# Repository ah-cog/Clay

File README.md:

Clay
====

Clay is an intelligent material that anyone can use to create interactive systems in objects and environments.

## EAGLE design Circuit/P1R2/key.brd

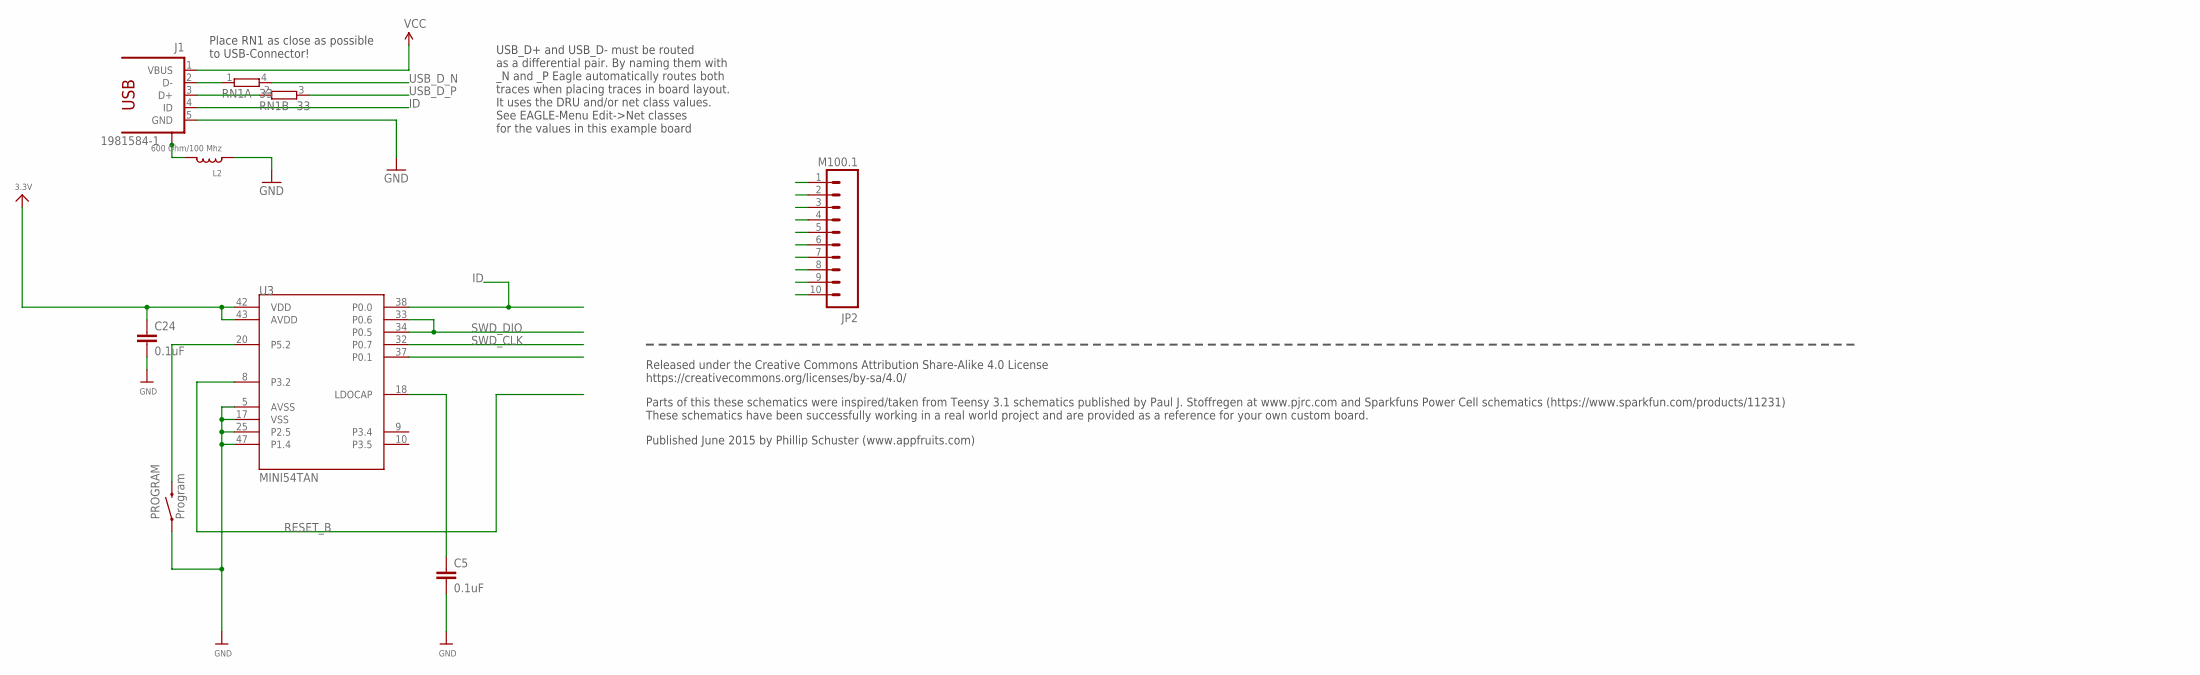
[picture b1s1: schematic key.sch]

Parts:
C5, C24: 0.1uF; 0603-CAP
J1: 1981584-1; MPN ZX62-AB-5PA(11)
JP2: M100.1; 1X10
L2: 600 Ohm/100 Mhz; 0805
PROGRAM: Program; TACTILE-SWITCH-1101NE; MPN RS-282G05A3-SM RT
RN1: 33; EXB34V; MPN EXB-34V330JV
U3: MINI54TAN

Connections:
3.3V: C24.1, JP2.10, U3.42 (VDD), U3.43 (AVDD)
GND: C5.2, C24.2, J1.5 (GND), JP2.1, L2.1, PROGRAM.P$1 (1), U3.5 (AVSS), U3.17 (VSS), U3.25 (P2.5), U3.47 (P1.4)
ID: J1.4 (ID), JP2.5, U3.38 (P0.0)
unnamed: PROGRAM.P$2 (2), U3.20 (P5.2)
unnamed: C5.1, U3.18 (LDOCAP)
P0.1: JP2.8, U3.37 (P0.1)
RESET_B: JP2.9, U3.8 (P3.2)
SWD_CLK: JP2.7, U3.32 (P0.7)
SWD_DIO: JP2.6, U3.33 (P0.6), U3.34 (P0.5)
USB_CON_N: J1.2 (D-), RN1.1
USB_CON_P: J1.3 (D+), RN1.2 (1)
USB_D_N: JP2.3, RN1.4 (2)
USB_D_P: JP2.4, RN1.3 (2)
USB_SHIELD: J1.S1, J1.S2, J1.S3, J1.S4, L2.2
VCC: J1.1 (VBUS), JP2.2

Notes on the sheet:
Place RN1 as close as possible to USB-Connector!
USB_D+ and USB_D- must be routed as a differential pair. By naming them with _N and _P Eagle automatically routes both traces when placing traces in board layout. It uses the DRU and/or net class values. See EAGLE-Menu Edit->Net classes for the values in this example board
Released under the Creative Commons Attribution Share-Alike 4.0 License https://creativecommons.org/licenses/by-sa/4.0/
Parts of this these schematics were inspired/taken from Teensy 3.1 schematics published by Paul J. Stoffregen at www.pjrc.com and Sparkfuns Power Cell schematics (https://www.sparkfun.com/products/11231) These schematics have been successfully working in a real world project and are provided as a r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
Published June 2015 by Phillip Schuster (www.appfruits.com)

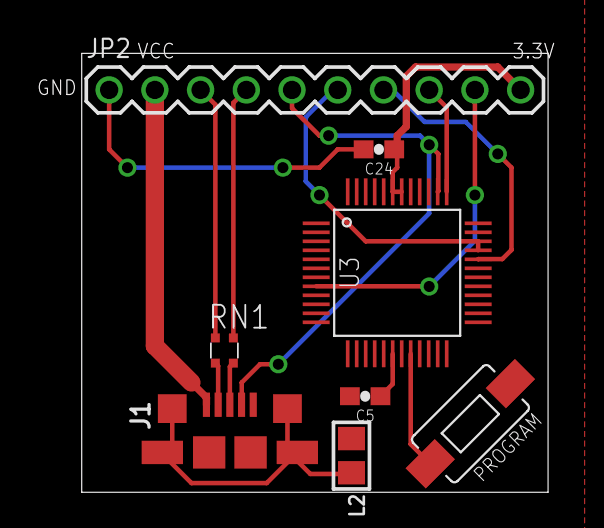
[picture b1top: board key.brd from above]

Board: 2 copper layers, 25.9 x 24.4 mm, 8 parts (0 on the bottom side), 15 nets.

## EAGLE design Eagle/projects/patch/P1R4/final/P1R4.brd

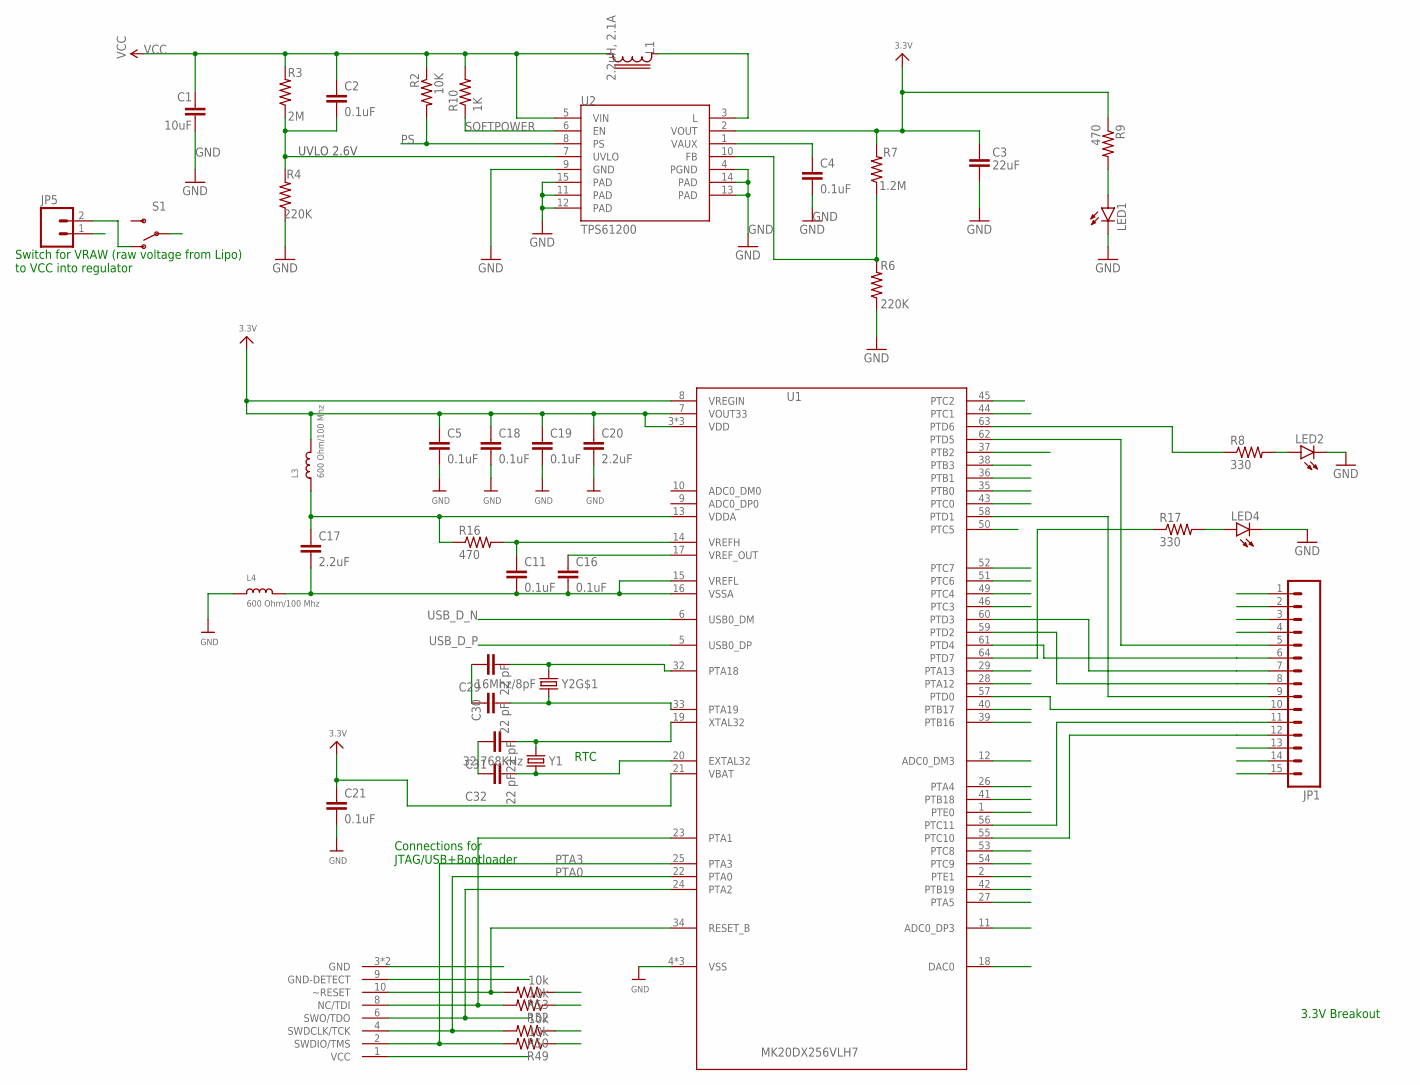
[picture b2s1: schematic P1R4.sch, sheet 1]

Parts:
C1: 10uF; 0603-CAP
C2, C4, C5, C11, C16, C18, C19, C21: 0.1uF; 0603-CAP
C3: 22uF; 0603-CAP
C17, C20: 2.2uF; 0603-CAP
C29, C30, C31, C32: 22 pF; 0603-CAP
JP1: M15; 1X15
JP5: M02PTH; 1X02
L1: 2.2uH, 2.1A; LPS3015
L3, L4: 600 Ohm/100 Mhz; 0805
LED1, LED2, LED4: LED-GREEN; LED-0603
R2: 10K; 0603-RES
R3: 2M; 0603-RES
R4, R6: 220K; 0603-RES
R7: 1.2M; 0603-RES
R8, R17: 330; 0603-RES
R9, R16: 470; 0603-RES
R10: 1K; 0603-RES
R49, R50, R52, R53: 10k; 0402-RES
S1: SWITCH-SPDT-SMD-A; SWITCH-SPST-SMD-A
U1: MK20DX256VLH7; MPN MK20DX256VLH7
U2: TPS61200; QFN-10_PAD
U$7: 2X5_0.05"_CORTEX_DEBUGTH_NOKEY_UNSHROUDED; 2X5_0.05"_TH_NS
Y1: 32.768KHz; CRYSTAL-TXC-7A; MPN FC-255 32.7680K-A3
Y2: 16Mhz/8pF; CRYSTAL-SMD-5X3; MPN ECS-160-8-30B-CKM

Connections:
3.3V: C3.1, C5.1, C18.1, C19.1, C20.1, C21.1, JP1.13, JP1.14, JP1.15, L3.2, R7.2, R9.1, R49.1, R52.1, R53.1, U1.3 (VDD), U1.7 (VOUT33), U1.8 (VREGIN), U1.21 (VBAT), U1.30 (VDD), U1.48 (VDD), U2.2 (VOUT), U$7.1 (VCC); also elsewhere on the board
A12: U1.11 (ADC0_DP3)
A13: U1.12 (ADC0_DM3)
AD0: U1.45 (PTC2); also elsewhere on the board
DAC/A14: U1.18 (DAC0)
FB: R6.2, R7.1, U2.10 (FB)
GND: C1.2, C3.2, C4.2, C5.2, C18.2, C19.2, C20.2, C21.2, C29.1, C30.1, C31.1, C32.1, JP1.1, JP1.2, JP1.3, JP1.4, JP5.1, L4.1, LED1.C, LED2.C, LED4.C, R4.1, R6.1, R50.1, U1.4 (VSS), U1.31 (VSS), U1.47 (VSS), U2.4 (PGND), U2.9 (GND), U2.11 (PAD), U2.12 (PAD), U2.13 (PAD), U2.14 (PAD), U2.15 (PAD), U$7.3 (GND), U$7.5 (GND), U$7.9 (GND-DETECT); also elsewhere on the board
unnamed: LED1.A, R9.2
unnamed: L1.1, U2.3 (L)
unnamed: LED2.A, R8.2
unnamed: C31.2, U1.19 (XTAL32), Y1.P$2 (2)
unnamed: C32.2, U1.20 (EXTAL32), Y1.P$1 (1)
unnamed: C29.2, U1.32 (PTA18), Y2.3 (2)
unnamed: C30.2, U1.33 (PTA19), Y2.1
unnamed: LED4.A, R17.2
PS: R2.2, U2.8 (PS)
PTA0: R50.2, U1.22 (PTA0), U$7.4 (SWDCLK/TCK)
PTA1: R52.2, U1.23 (PTA1), U$7.8 (NC/TDI)
PTA2: U1.24 (PTA2), U$7.6 (SWO/TDO)
PTA3: R49.2, U1.25 (PTA3), U$7.2 (SWDIO/TMS)
PTA4: U1.26 (PTA4)
PTA5: U1.27 (PTA5)
PTA12: U1.28 (PTA12)
PTA13: U1.29 (PTA13)
PTB0: U1.35 (PTB0); also elsewhere on the board
PTB1: U1.36 (PTB1); also elsewhere on the board
PTB16: U1.39 (PTB16); also elsewhere on the board
PTB17: U1.40 (PTB17); also elsewhere on the board
PTB18: U1.41 (PTB18); also elsewhere on the board
PTB19: U1.42 (PTB19); also elsewhere on the board
PTC0: U1.43 (PTC0); also elsewhere on the board
PTC1: U1.44 (PTC1); also elsewhere on the board
PTC3: U1.46 (PTC3); also elsewhere on the board
PTC4: U1.49 (PTC4); also elsewhere on the board
PTC5: U1.50 (PTC5); also elsewhere on the board
PTC6: U1.51 (PTC6); also elsewhere on the board
PTC7: U1.52 (PTC7); also elsewhere on the board
PTC8: U1.53 (PTC8); also elsewhere on the board
PTC9: U1.54 (PTC9); also elsewhere on the board
PTC10: JP1.12, U1.55 (PTC10)
PTC11: JP1.11, U1.56 (PTC11)
PTD0: JP1.10, U1.57 (PTD0)
PTD1: JP1.9, U1.58 (PTD1)
PTD2: JP1.8, U1.59 (PTD2)
PTD3: JP1.7, U1.60 (PTD3)
PTD4: JP1.6, U1.61 (PTD4)
PTD5: JP1.5, U1.62 (PTD5)
PTD6: R8.1, U1.63 (PTD6)
PTD7: R17.1, U1.64 (PTD7)
PTE0: U1.1 (PTE0)
PTE1: U1.2 (PTE1)
RESET_B: R53.2, U1.34 (RESET_B), U$7.10 (~RESET)
SCL: U1.37 (PTB2); also elsewhere on the board
SDA: U1.38 (PTB3); also elsewhere on the board
SOFTPOWER: R10.1, U2.6 (EN)
USB_D_N: U1.6 (USB0_DM)
USB_D_P: U1.5 (USB0_DP)
UVLO: C2.2, R3.1, R4.2, U2.7 (UVLO)
VAUX: C4.1, U2.1 (VAUX)
VCC: C1.1, C2.1, L1.2, R2.1, R3.2, R10.2, S1.2, U2.5 (VIN)
VDDA: C17.1, L3.1, R16.1, U1.13 (VDDA)
VRAW: JP5.2, S1.1 (O)
VREFH: C11.1, R16.2, U1.14 (VREFH)
VREFL: C11.2, C16.2, C17.2, L4.2, U1.15 (VREFL), U1.16 (VSSA)
VREF_OUT: C16.1, U1.17 (VREF_OUT)

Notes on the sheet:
UVLO 2.6V
Switch for VRAW (raw voltage from Lipo) to VCC into regulator
Connections for JTAG/USB+Bootloader
RTC
3.3V Breakout

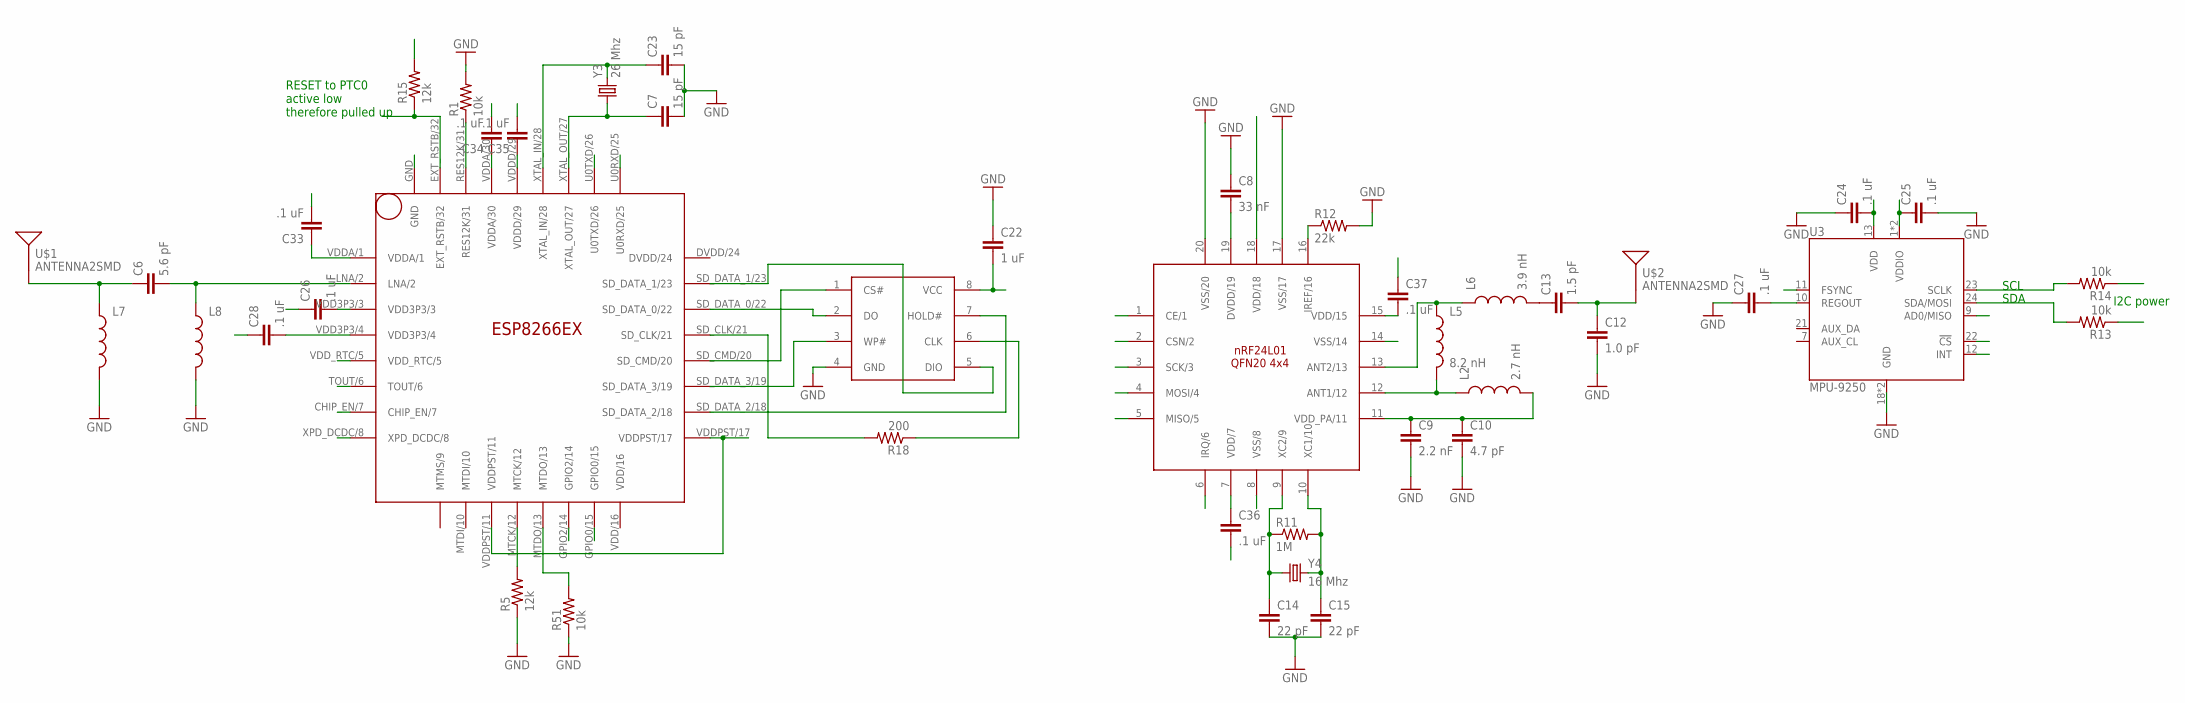
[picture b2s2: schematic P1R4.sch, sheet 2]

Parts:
C6: 5.6 pF; 0603-CAP
C7, C23: 15 pF; 0603-CAP
C8: 33 nF; 0603-CAP
C9: 2.2 nF; 0603-CAP
C10: 4.7 pF; 0603-CAP
C12: 1.0 pF; 0603-CAP
C13: 1.5 pF; 0603-CAP
C14, C15: 22 pF; 0603-CAP
C22: 1 uF; 0603-CAP
C24, C25, C26, C27, C28, C33, C34, C35, C36, C37: .1 uF; 0603-CAP
L2: 2.7 nH; C0402
L5: 8.2 nH; C0402
L6: 3.9 nH; C0402
L7, L8: INDUCTOR30OHM,1.8A; 0603
R1, R13, R14, R51: 10k; 0603-RES
R5, R15: 12k; 0603-RES
R11: 1M; 0603-RES
R12: 22k; 0603-RES
R18: 200; 0603-RES
U3: MPU-9250; QFN-24/3MM
U$1, U$2: ANTENNA2SMD; ANTENNA-CHIP2
U$3: 25Q40; SOP8
U$4: NRF24L01; QFN20(4X4)
U$6: ESP8266EX; QFN32
Y3: 26 Mhz; CRYSTAL-SMD-5X3
Y4: 16 Mhz; CRYSTAL-SMD-5X3

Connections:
3.3V: C22.2, C24.2, C25.1, C26.2, C28.2, C33.1, C34.1, C35.1, C36.1, C37.2, R13.1, R14.1, R15.2, U3.1 (VDDIO), U3.8 (VDDIO), U3.13 (VDD), U3.22 (!CS), U$3.8 (VCC), U$4.7 (VDD/7), U$4.15 (VDD/15), U$4.18 (VDD/18), U$6.VDD3P3/3, U$6.VDD3P3/4, U$6.VDDA/1, U$6.VDDA/30, U$6.VDDD/29, U$6.VDDPST/11, U$6.VDDPST/17; also elsewhere on the board
AD0: U3.9 (AD0/MISO); also elsewhere on the board
GND: C7.2, C8.1, C9.2, C10.2, C12.2, C14.2, C15.2, C22.1, C23.2, C24.1, C25.2, C26.1, C27.1, C28.1, C33.2, C34.2, C35.2, C36.2, C37.1, L7.2, L8.2, R1.2, R5.1, R12.2, R51.1, U3.18 (GND), U3.20 (GND), U$3.4 (GND), U$4.8 (VSS/8), U$4.14 (VSS/14), U$4.17 (VSS/17), U$4.20 (VSS/20), U$6.GND; also elsewhere on the board
MTDO: R51.2, U$6.MTDO/13
unnamed: C6.2, L8.1, U$6.LNA/2
unnamed: C6.1, L7.1, U$1.FEED
unnamed: C14.1, R11.1, U$4.9 (XC2/9), Y4.1
unnamed: C15.1, R11.2, U$4.10 (XC1/10), Y4.3 (2)
unnamed: C9.1, C10.1, L2.2, U$4.11 (VDD_PA/11)
unnamed: L5.1, L6.1, U$4.13 (ANT2/13)
unnamed: C8.2, U$4.19 (DVDD/19)
unnamed: L2.1, L5.2, U$4.12 (ANT1/12)
unnamed: R12.1, U$4.16 (IREF/16)
unnamed: C13.1, L6.2
unnamed: C12.1, C13.2, U$2.FEED
unnamed: R5.2, U$6.MTCK/12
unnamed: C27.2, U3.10 (REGOUT)
unnamed: R18.1, U$3.6 (CLK)
unnamed: R1.1, U$6.RES12K/31
PTB0: U3.12 (INT); also elsewhere on the board
PTB1: U3.11 (FSYNC); also elsewhere on the board
PTB16: U$6.U0TXD/26; also elsewhere on the board
PTB17: U$6.U0RXD/25; also elsewhere on the board
PTB18: U$6.GPIO0/15; also elsewhere on the board
PTB19: U$6.GPIO2/14; also elsewhere on the board
PTC0: R15.1, U$6.EXT_RSTB/32; also elsewhere on the board
PTC1: U$6.CHIP_EN/7; also elsewhere on the board
PTC3: U$6.XPD_DCDC/8; also elsewhere on the board
PTC4: U$4.2 (CSN/2); also elsewhere on the board
PTC5: U$4.3 (SCK/3); also elsewhere on the board
PTC6: U$4.4 (MOSI/4); also elsewhere on the board
PTC7: U$4.5 (MISO/5); also elsewhere on the board
PTC8: U$4.6 (IRQ/6); also elsewhere on the board
PTC9: U$4.1 (CE/1); also elsewhere on the board
RTC: U$6.VDD_RTC/5
SCL: R14.2, U3.23 (SCLK); also elsewhere on the board
SD-CLK: R18.2, U$6.SD_CLK/21
SD-CMD: U$3.1 (CS#), U$6.SD_CMD/20
SD-D0: U$3.2 (DO), U$6.SD_DATA_0/22
SD-D1: U$3.5 (DIO), U$6.SD_DATA_1/23
SD-D2: U$3.7 (HOLD#), U$6.SD_DATA_2/18
SD-D3: U$3.3 (WP#), U$6.SD_DATA_3/19
SDA: R13.2, U3.24 (SDA/MOSI); also elsewhere on the board
TOUT: U$6.TOUT/6
XTAL_IN: C23.1, U$6.XTAL_IN/28, Y3.3 (2)
XTAL_OUT: C7.1, U$6.XTAL_OUT/27, Y3.1

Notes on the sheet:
I2C power
SDA
SCL
RESET to PTC0 active low therefore pulled up

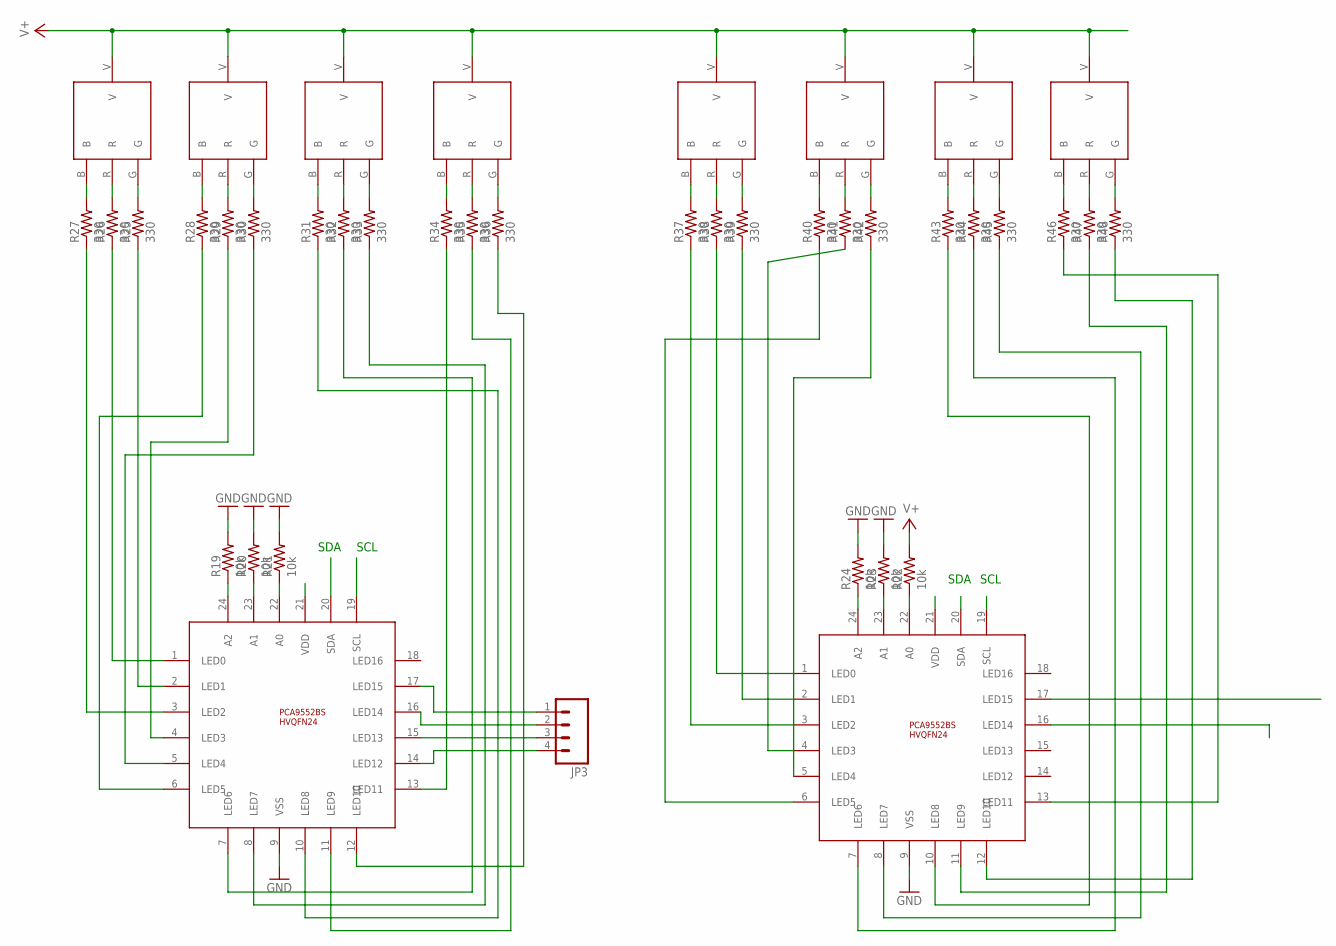
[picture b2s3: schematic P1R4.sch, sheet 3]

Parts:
JP3: M04PTH; 1X04
R19, R20, R21, R22, R23, R24: 10k; 0603-RES
R25, R26, R27, R28, R29, R30, R31, R32, R33, R34, R35, R36, R37, R38, R39, R40, R41, R42, R43, R44, R45, R46, R47, R48: 330; 0402-RES
U$8, U$11, U$13, U$14, U$15, U$16, U$17, U$18: LTST-C19FD1WT
U$20, U$21: PCA9552BS; HVQFN24

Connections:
3.3V: R22.2, U$8.V, U$11.V, U$13.V, U$14.V, U$15.V, U$16.V, U$17.V, U$18.V, U$20.21 (VDD), U$21.21 (VDD); also elsewhere on the board
GND: R19.2, R20.2, R21.2, R23.2, R24.2, U$20.9 (VSS), U$21.9 (VSS); also elsewhere on the board
unnamed: JP3.3, U$20.15 (LED13)
unnamed: R26.2, U$8.R
unnamed: R19.1, U$20.24 (A2)
unnamed: R27.2, U$8.B
unnamed: R25.2, U$8.G
unnamed: R28.2, U$11.B
unnamed: R29.2, U$11.R
unnamed: R30.2, U$11.G
unnamed: R27.1, U$20.3 (LED2)
unnamed: R26.1, U$20.1 (LED0)
unnamed: R31.2, U$13.B
unnamed: R28.1, U$20.6 (LED5)
unnamed: R32.2, U$13.R
unnamed: R33.2, U$13.G
unnamed: R34.2, U$14.B
unnamed: R35.2, U$14.R
unnamed: R25.1, U$20.2 (LED1)
unnamed: R29.1, U$20.4 (LED3)
unnamed: R30.1, U$20.5 (LED4)
unnamed: R32.1, U$20.7 (LED6)
unnamed: R33.1, U$20.8 (LED7)
unnamed: R31.1, U$20.10 (LED8)
unnamed: R36.2, U$14.G
unnamed: R35.1, U$20.11 (LED9)
unnamed: R36.1, U$20.12 (LED10)
unnamed: R34.1, U$20.13 (LED11)
unnamed: JP3.4, U$20.14 (LED12)
unnamed: R37.2, U$15.B
unnamed: R20.1, U$20.23 (A1)
unnamed: R21.1, U$20.22 (A0)
unnamed: R38.2, U$15.R
unnamed: JP3.2, U$20.16 (LED14)
unnamed: R38.1, U$21.1 (LED0)
unnamed: R39.1, U$21.2 (LED1)
unnamed: R37.1, U$21.3 (LED2)
unnamed: R41.1, U$21.4 (LED3)
unnamed: R42.1, U$21.5 (LED4)
unnamed: R40.1, U$21.6 (LED5)
unnamed: R44.1, U$21.7 (LED6)
unnamed: R45.1, U$21.8 (LED7)
unnamed: R39.2, U$15.G
unnamed: R43.1, U$21.10 (LED8)
unnamed: R47.1, U$21.11 (LED9)
unnamed: R48.1, U$21.12 (LED10)
unnamed: R46.1, U$21.13 (LED11)
unnamed: JP3.1, U$20.17 (LED15)
unnamed: R24.1, U$21.24 (A2)
unnamed: R23.1, U$21.23 (A1)
unnamed: R22.1, U$21.22 (A0)
unnamed: R40.2, U$16.B
unnamed: R41.2, U$16.R
unnamed: R42.2, U$16.G
unnamed: R43.2, U$17.B
unnamed: R44.2, U$17.R
unnamed: R45.2, U$17.G
unnamed: R46.2, U$18.B
unnamed: R47.2, U$18.R
unnamed: R48.2, U$18.G
SCL: U$20.19 (SCL), U$21.19 (SCL); also elsewhere on the board
SDA: U$20.20 (SDA), U$21.20 (SDA); also elsewhere on the board

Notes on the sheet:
SDA
SCL

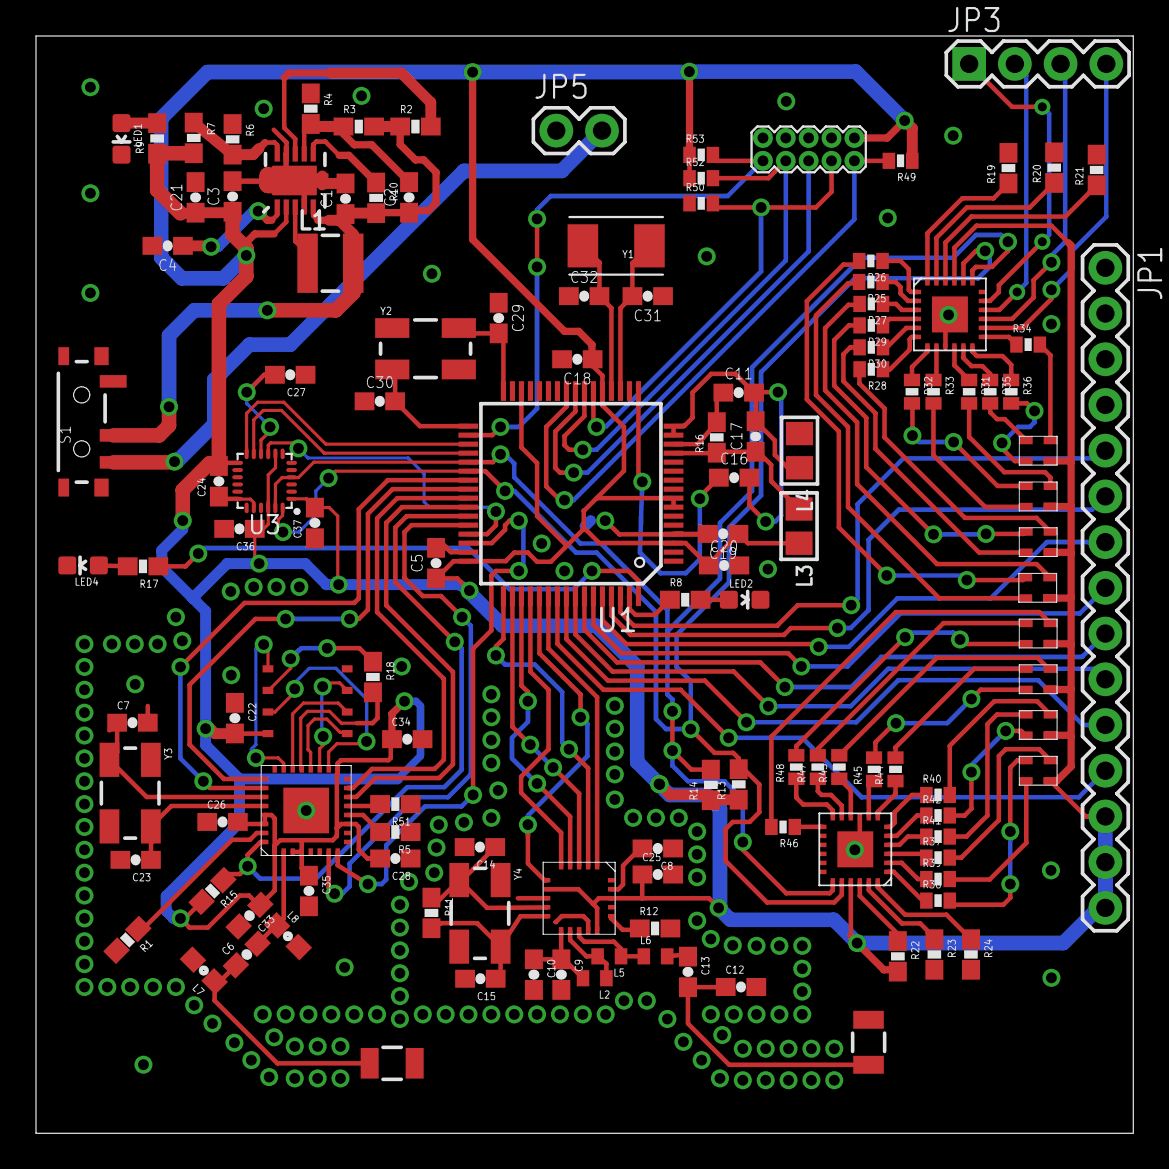
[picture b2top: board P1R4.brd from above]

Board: 2 copper layers, 61.0 x 61.0 mm, 128 parts (0 on the bottom side), 136 nets.

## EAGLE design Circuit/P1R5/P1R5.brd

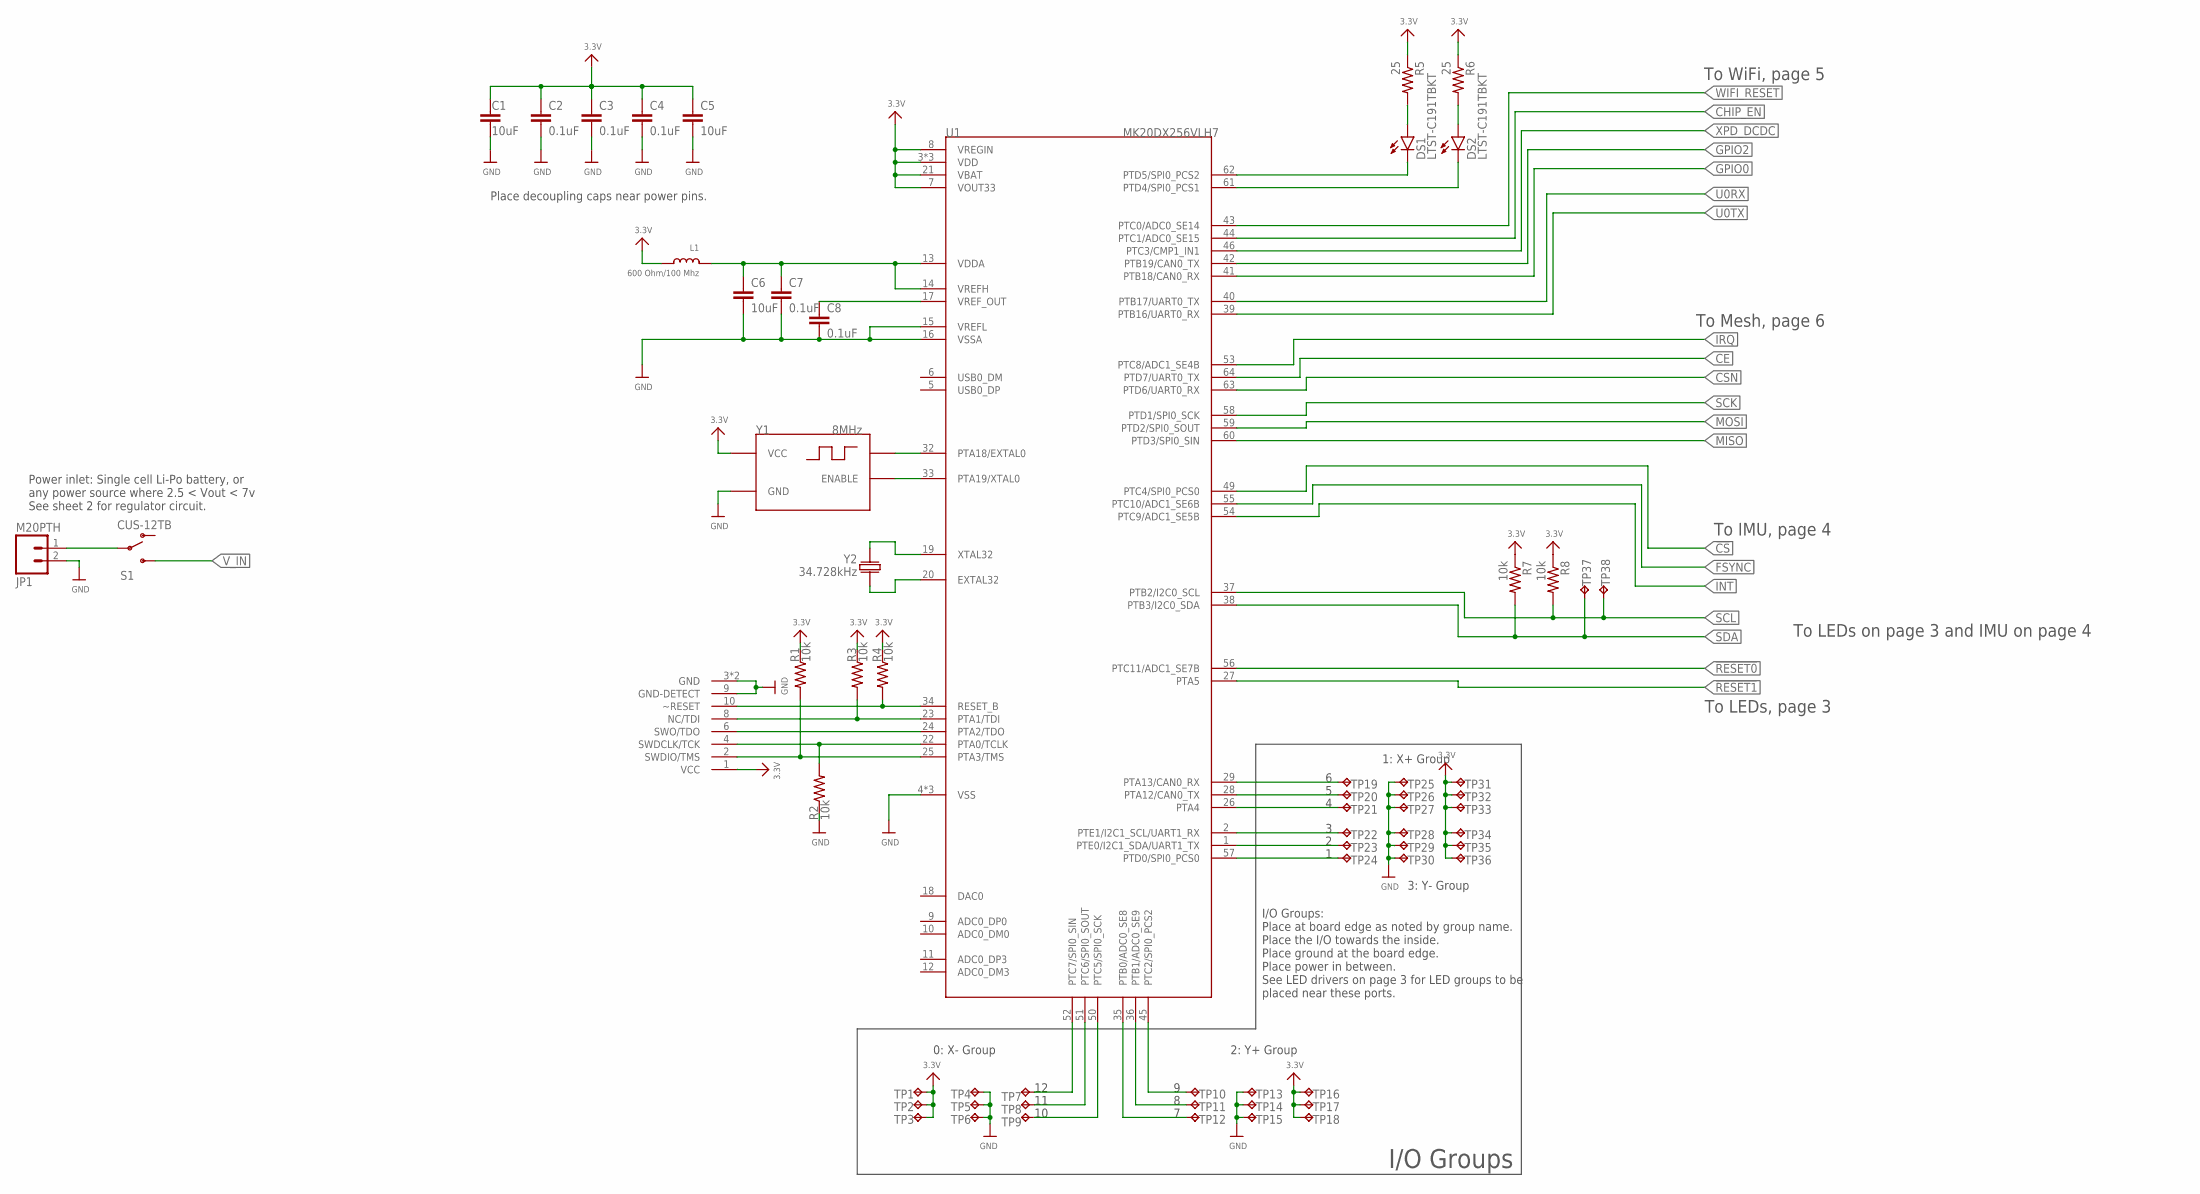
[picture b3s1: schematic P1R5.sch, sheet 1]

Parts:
C1, C5, C6: 10uF; 0603-CAP; PARTNO C1608X7S0J106M080AC
C2, C3, C4, C7, C8: 0.1uF; 0402-CAP; PARTNO C1005X7R1C104K050BC
DS1, DS2: LTST-C191TBKT; LED-0603; PARTNO LTST-C191TBKT
J1: 2X5_0.05"_CORTEX_DEBUGTH_NOKEY_UNSHROUDED; 2X5_0.05"_TH_NS; PARTNO 20021111-00010T4LF
JP1: M20PTH; JST_2PIN; PARTNO S2B-PH-K-S(LF)(SN)
L1: 600 Ohm/100 Mhz; 0805; PARTNO BK2125HM601-T
R1, R2, R3, R4, R7, R8: 10k; _0402; PARTNO CRCW040210K0FKED
R5, R6: 25; _0402; PARTNO CRCW040224R9FKED
S1: CUS-12TB; SWITCH-SPST-SMD-A; PARTNO CUS-12TB
TP1, TP2, TP3, TP4, TP5, TP6, TP7, TP8, TP9, TP10, TP11, TP12, TP13, TP14, TP15, TP16, TP17, TP18, TP19, TP20, TP21, TP22, TP23, TP24, TP25, TP26, TP27, TP28, TP29, TP30, TP31, TP32, TP33, TP34, TP35, TP36: TPPAD1-13; P1-13; PARTNO TEST POINT
TP37, TP38: TPTP08R; TP08R; PARTNO TEST POINT
U1: MK20DX256VLH7; MPN MK20DX256VLH7
Y1: 8MHz; ASCO; PARTNO ASCO-8.000MHZ-EK-T3
Y2: 34.728kHz; ABS06; PARTNO ABS06-32.768KHZ-T

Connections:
3.3V: C1.1, C2.1, C3.1, C4.1, C5.1, J1.1 (VCC), L1.2, R1.1, R3.1, R4.1, R5.1, R6.1, R7.1, R8.1, TP1.TP, TP2.TP, TP3.TP, TP16.TP, TP17.TP, TP18.TP, TP31.TP, TP32.TP, TP33.TP, TP34.TP, TP35.TP, TP36.TP, U1.3 (VDD), U1.7 (VOUT33), U1.8 (VREGIN), U1.21 (VBAT), U1.30 (VDD), U1.48 (VDD), Y1.VCC; also elsewhere on the board
!CS: U1.49 (PTC4/SPI0_PCS0); also elsewhere on the board
!RESET0: U1.56 (PTC11/ADC1_SE7B); also elsewhere on the board
!RESET1: U1.27 (PTA5); also elsewhere on the board
CE: U1.64 (PTD7/UART0_TX); also elsewhere on the board
CHIP_EN: U1.44 (PTC1/ADC0_SE15); also elsewhere on the board
CSN: U1.63 (PTD6/UART0_RX); also elsewhere on the board
FSYNC: U1.55 (PTC10/ADC1_SE6B); also elsewhere on the board
GND: C1.2, C2.2, C3.2, C4.2, C5.2, C6.2, C7.2, C8.2, J1.3 (GND), J1.5 (GND), J1.9 (GND-DETECT), JP1.2, R2.1, TP4.TP, TP5.TP, TP6.TP, TP13.TP, TP14.TP, TP15.TP, TP25.TP, TP26.TP, TP27.TP, TP28.TP, TP29.TP, TP30.TP, U1.4 (VSS), U1.15 (VREFL), U1.16 (VSSA), U1.31 (VSS), U1.47 (VSS), Y1.GND; also elsewhere on the board
GPIO0: U1.41 (PTB18/CAN0_RX); also elsewhere on the board
GPIO2: U1.42 (PTB19/CAN0_TX); also elsewhere on the board
INT: U1.54 (PTC9/ADC1_SE5B); also elsewhere on the board
IRQ: U1.53 (PTC8/ADC1_SE4B); also elsewhere on the board
MISO: U1.60 (PTD3/SPI0_SIN); also elsewhere on the board
MOSI: U1.59 (PTD2/SPI0_SOUT); also elsewhere on the board
unnamed: U1.32 (PTA18/EXTAL0), Y1.OUT
unnamed: U1.33 (PTA19/XTAL0), Y1.ENABLE
unnamed: TP7.TP, U1.52 (PTC7/SPI0_SIN)
unnamed: TP8.TP, U1.51 (PTC6/SPI0_SOUT)
unnamed: DS1.A, R5.2
unnamed: U1.19 (XTAL32), Y2.P$2 (2)
unnamed: U1.20 (EXTAL32), Y2.P$1 (1)
unnamed: DS1.C, U1.62 (PTD5/SPI0_PCS2)
unnamed: TP9.TP, U1.50 (PTC5/SPI0_SCK)
unnamed: TP10.TP, U1.45 (PTC2/SPI0_PCS2)
unnamed: DS2.C, U1.61 (PTD4/SPI0_PCS1)
unnamed: TP11.TP, U1.36 (PTB1/ADC0_SE9)
unnamed: TP12.TP, U1.35 (PTB0/ADC0_SE8)
unnamed: TP24.TP, U1.57 (PTD0/SPI0_PCS0)
unnamed: TP21.TP, U1.26 (PTA4)
unnamed: TP22.TP, U1.2 (PTE1/I2C1_SCL/UART1_RX)
unnamed: TP23.TP, U1.1 (PTE0/I2C1_SDA/UART1_TX)
unnamed: TP19.TP, U1.29 (PTA13/CAN0_RX)
unnamed: TP20.TP, U1.28 (PTA12/CAN0_TX)
unnamed: DS2.A, R6.2
unnamed: JP1.1, S1.2
PTA0: J1.4 (SWDCLK/TCK), R2.2, U1.22 (PTA0/TCLK)
PTA1: J1.8 (NC/TDI), R3.2, U1.23 (PTA1/TDI)
PTA2: J1.6 (SWO/TDO), U1.24 (PTA2/TDO)
PTA3: J1.2 (SWDIO/TMS), R1.2, U1.25 (PTA3/TMS)
RESET_B: J1.10 (~RESET), R4.2, U1.34 (RESET_B)
SCK: U1.58 (PTD1/SPI0_SCK); also elsewhere on the board
SCL: R8.2, TP38.TP, U1.37 (PTB2/I2C0_SCL); also elsewhere on the board
SDA: R7.2, TP37.TP, U1.38 (PTB3/I2C0_SDA); also elsewhere on the board
U0RX: U1.40 (PTB17/UART0_TX); also elsewhere on the board
U0TX: U1.39 (PTB16/UART0_RX); also elsewhere on the board
VDDA: C6.1, C7.1, L1.1, U1.13 (VDDA), U1.14 (VREFH)
VREF_OUT: C8.1, U1.17 (VREF_OUT)
V_IN: S1.3 (S); also elsewhere on the board
WIFI_RESET: U1.43 (PTC0/ADC0_SE14); also elsewhere on the board
XPD_DCDC: U1.46 (PTC3/CMP1_IN1); also elsewhere on the board

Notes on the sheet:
Power inlet: Single cell Li-Po battery, or any power source where 2.5 < Vout < 7v See sheet 2 for regulator circuit.
Place decoupling caps near power pins.
0: X- Group
2: Y+ Group
1: X+ Group
3: Y- Group
I/O Groups: Place at board edge as noted by group name. Place the I/O towards the inside. Place ground at the board edge. Place power in between. See LED drivers on page 3 for LED groups to be placed near these ports.
I/O Groups
To WiFi, page 5
To Mesh, page 6
To IMU, page 4
To LEDs, page 3
To LEDs on page 3 and IMU on page 4

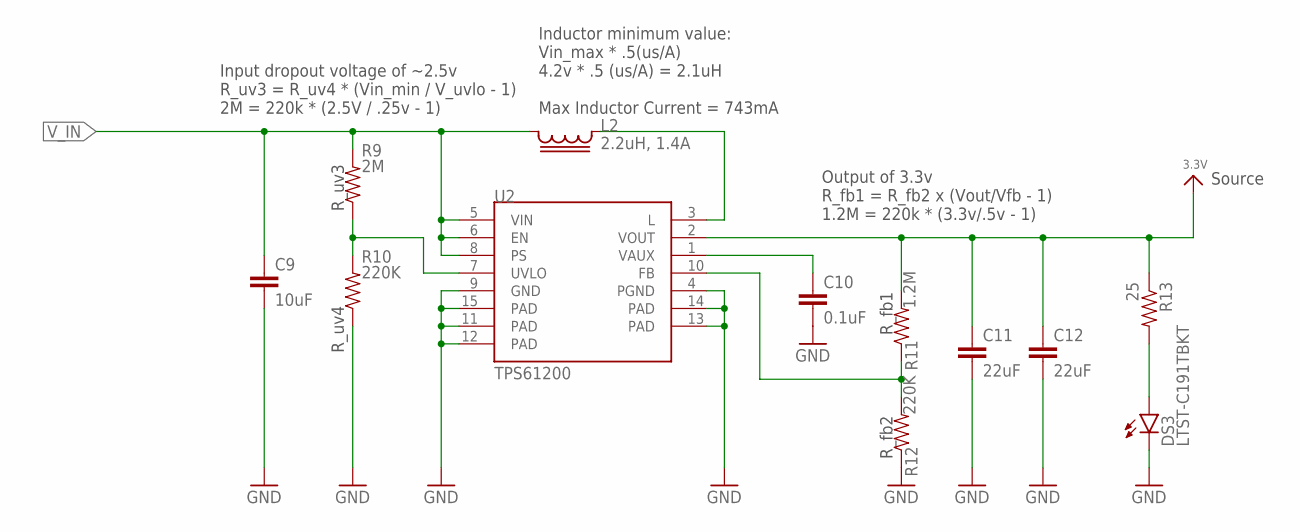
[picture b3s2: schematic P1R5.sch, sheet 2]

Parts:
C9: 10uF; 0603-CAP; PARTNO C1608X7S0J106M080AC
C10: 0.1uF; 0402-CAP; PARTNO C1005X7R1C104K050BC
C11, C12: 22uF; 1210; PARTNO C3225X7R1A226K230AC
DS3: LTST-C191TBKT; LED-0603; PARTNO LTST-C191TBKT
L2: 2.2uH, 1.4A; LPS3015; PARTNO BRL3225T2R2M
R9: 2M; _0402; PARTNO CRCW04022M00FKED
R10, R12: 220K; _0402; PARTNO CRCW0402220KFKED
R11: 1.2M; _0402; PARTNO CRCW04021M20FKED
R13: 25; _0402; PARTNO CRCW040224R9FKED
U2: TPS61200; QFN-10_PAD; PARTNO TPS61200DRCR

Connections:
3.3V: C11.1, C12.1, R11.2, R13.1, U2.2 (VOUT); also elsewhere on the board
GND: C9.2, C10.2, C11.2, C12.2, DS3.C, R10.1, R12.1, U2.4 (PGND), U2.9 (GND), U2.11 (PAD), U2.12 (PAD), U2.13 (PAD), U2.14 (PAD), U2.15 (PAD); also elsewhere on the board
unnamed: L2.1, U2.3 (L)
unnamed: C10.1, U2.1 (VAUX)
unnamed: R9.1, R10.2, U2.7 (UVLO)
unnamed: R11.1, R12.2, U2.10 (FB)
unnamed: DS3.A, R13.2
V_IN: C9.1, L2.2, R9.2, U2.5 (VIN), U2.6 (EN), U2.8 (PS); also elsewhere on the board

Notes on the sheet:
Output of 3.3v R_fb1 = R_fb2 x (Vout/Vfb - 1) 1.2M = 220k * (3.3v/.5v - 1)
R_fb1
R_fb2
R_uv3
R_uv4
Input dropout voltage of ~2.5v R_uv3 = R_uv4 * (Vin_min / V_uvlo - 1) 2M = 220k * (2.5V / .25v - 1)
Inductor minimum value: Vin_max * .5(us/A) 4.2v * .5 (us/A) = 2.1uH Max Inductor Current = 743mA
Source

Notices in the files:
parts and their libraries:
con-usb: Copyright (C) 2008, Bob Starr
SparkFun-Electromechanical: Licensing: Creative Commons ShareAlike 4.0 International - https://creativecommons.org/licenses/by-sa/4.0
